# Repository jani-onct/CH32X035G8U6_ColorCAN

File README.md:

# ColorCAN

**ColorCANは，CH32X035G8U6内蔵のPIOCで1 MbpsのClassic CAN送信を実装したカラーセンサ基板です．** TCS34725FNで測定した赤・緑・青・Clearの値を送信します．基板シルクは **v1.0.0**，CANのハートビートで通知するプロトコル版は **1** です．

基板の配置図はKiCadの3D表示です．この表示ではカラーセンサとマイコンの実装位置がパッドで見えます．DIPスイッチの操作方向は，基板のシルクにある `ON=1` と `TERM ON` を参照してください．

## PIOCによるCAN送信

**PIOC（Programmable Protocol I/O Controller）** は，CH32X035に内蔵されたI/O制御用の8ビットコアです．メインCPUから独立して命令を実行し，ピンの出力と読み取りのタイミングをクロック単位で制御できます．[WCHのPIOC解説](https://www.cnblogs.com/wchmcu/p/17678765.html)

ColorCANのPIOC版FWでは，メインCPUがセンサを読み取り，CANフレームを組み立てます．PIOCはPC19（TX）からフレームを1ビットずつ出力し，PC18（RX）でバスの状態を読み返してACKを確認します．SN65HVD230がCAN_HとCAN_Lの差動信号を扱います．

## 動作の様子

<p><a href="https://github.com/jani-onct/CH32X035G8U6_ColorCAN/issues/1#issue-6348853291" target="_blank">動作の様子(動画)</a></p>

## 基板仕様

| 項目 | 仕様 |
|---|---|
| 外形・取付穴 | 30 × 28 mm，四隅に直径3.2 mmのM3用取付穴．穴の中心間隔は横24 mm × 縦22 mm |
| マイコン | WCH CH32X035G8U6，QFN-28 |
| カラーセンサ | ams OSRAM TCS34725FN．I²Cの7-bitアドレスは `0x29`．試験FWは積分時間50.4 ms，ゲイン1倍 |
| 照明・電源表示 | センサ両側の白色LED 2個，電源表示の赤色LED 1個 |
| 電源 | 5 V入力．XC6206P332MR-Gで基板内の3.3 Vを生成 |
| USB-C（J1） | 5 V給電，USB ISP書き込み，仮想COMでのデバッグ |
| CAN（J2） | JST XA 4極，2.5 mmピッチ，横型（S04B-XASK-1）．SN65HVD230使用，Rsは10 kΩでGNDへ接続 |
| DIP（SW1） | [OTAX KHS42E（秋月電子・108929）](https://akizukidenshi.com/catalog/g/g108929/)，4連．3連でノード番号，1連で120 ΩのCAN終端を設定 |

## 配線とDIP設定

**DIP面を手前にして，XAコネクタを下**に向けたとき，J2のピンは左から次の順です．

| ピン | シルク | 信号 |
|---:|---|---|
| 1 | `GND` | 電源・CAN共通GND |
| 2 | `+5V` | 5 V電源入力 |
| 3 | `L` | CAN_L |
| 4 | `H` | CAN_H |

**USB-CのVBUSとJ2の+5Vは基板上で同じネットです．給電元は片方にしてください．** USB給電でCANを試す場合は，J2のGND・CAN_L・CAN_Hを接続し，J2の+5Vを開放します．J2給電中にUSBデバッグする場合は，VBUSを切ったデータ用USBケーブルを使用します．

XAコネクタを下にした状態で，**左に倒すとON，右に倒すとOFF**です．上の3段で送信するCAN IDを選び，変更後に電源を入れ直します．

| 最上段（基板の `1`） | 2段目（`2`） | 3段目（`4`） | ノード番号 | RGBCのCAN ID | ハートビートのCAN ID |
|---|---|---|---:|---|---|
| OFF | OFF | OFF | 0 | `0x240` | `0x248` |
| ON | OFF | OFF | 1 | `0x241` | `0x249` |
| OFF | ON | OFF | 2 | `0x242` | `0x24A` |
| OFF | OFF | ON | 4 | `0x244` | `0x24C` |
| ON | OFF | ON | 5 | `0x245` | `0x24D` |
| OFF | ON | ON | 6 | `0x246` | `0x24E` |
| ON | ON | ON | 7 | `0x247` | `0x24F` |

一番下の `TERM` は120 Ω終端のスイッチです．CANバスの両端でONにします．

## CANを受信する

**1 Mbps，Classic CAN，標準11-bit ID，データ長8バイト．** 複数バイトの数値は下位バイトから並びます．

| フレーム | 送信タイミング |
|---|---|
| RGBC | 有効な測定値を取得できたとき，100 msごと |
| ハートビート | 約1秒ごと，またはセンサ状態が変化したとき |

1. ColorCAN 1台と，1 MbpsのCAN受信機1台を短い配線でつなぎます．CAN_H同士，CAN_L同士，GND同士を接続し，両端を120 Ωで終端します．
2. 受信機を通常モード（ACKあり）に設定します．まずID用DIPをすべてOFFにしてColorCANを起動すると，ノード番号は `0` です．
3. USB-CANアダプターなどの受信ツールで，`0x240` のRGBCと `0x248` のハートビートを確認します．

### CANメッセージの例

ID用DIPをすべてOFFにしたときの例です．

```text
CAN ID  DLC  データ（16進）
0x240     8  AB 00 B5 00 B8 00 14 02
0x248     8  01 01 0B 00 61 04 00 00
```

- **`0x240` RGBC** — 2バイトずつ読むと，R = 171，G = 181，B = 184，Clear = 532．
- **`0x248` ハートビート** — プロトコル版1，測定有効，測定成功11回，起動から1,121 ms．

各FWは**ColorCAN 1台が送信するベンチ試験用**です．複数の送信ノードが共存する運用バスに組み込むには，CANの調停，再送，エラー処理を備えた実装が必要です．ベンチ試験ではノード0の両フレームを受信確認済みです．

- [CAN仕様とデコード例](docs/CAN.md)
- [CANデータベース（DBC，ノード0〜7）](docs/ColorCAN.dbc)

### ch32fun版のTIM1＋DMAとPIOCのメモリ使用量

各FWのCAN ID，RGBCとハートビートのデータ形式，送信周期は共通です．

| ビルド時の使用量 | TIM1＋DMA版 | PIOC版 | 差（PIOC版 − TIM1＋DMA版） |
|---|---:|---:|---:|
| Flash | 7,112 B | 7,148 B | +36 B |
| メインCPUの静的RAM（`.data`＋`.bss`） | 1,564 B | 472 B | −1,092 B |
| メインCPUのRAM残り（スタック使用前） | 18,916 B | 15,912 B | −3,004 B |

PIOC版では，送受信に使っていたDMAバッファ計1,080 Bが不要になり，TIM1とDMAの2チャネルが空きます．PIOC命令は184 Bです．メインCPU用のRAMは16 KiBで，残りの4 KiBをPIOC用に予約しています．メインCPUは送信完了をポーリングします．CPU負荷とスタックのピーク使用量は未計測です．

ch32funのPIOC版を使った実機試験では，ノード0のRGBC（`0x240`）とハートビート（`0x248`）が1 Mbpsの受信機に届き，RGBCの受信カウンタが増えることを確認しました．

## ファームウェアの書き込み

ColorCAN v1.0.0（CH32X035G8U6）用です．ch32fun版は実機でCANを受信確認済みです．Arduino版はUSB ISPでの書き込みとベリファイを確認済みです．

| 実装 | 書き込み用HEX | SHA-256 |
|---|---|---|
| TIM1＋DMA版 | [colorcan_can_bench.hex](firmware/colorcan_can_bench.hex) | `e5137b95454fce0f72337260dc35df75672d55e5464d6f02d0543154b2a608ff` |
| PIOC版（ch32fun） | [colorcan_can_pioc.hex](firmware/colorcan_can_pioc.hex) | `1e422510251ff6a533be32441a781ffb076a6dc97d74cc8b8e29d4a9e3a904bd` |
| PIOC版（Arduino） | [colorcan_can_pioc_arduino.hex](firmware/colorcan_can_pioc_arduino.hex) | `d5f5aad851115a2fc54eebe81fec8b35ea951dc252fb6bb9a10da01881828f88` |

Arduino版のソースとビルド手順は[Arduino版FWの説明](firmware/arduino/README.md)を参照してください．

1. J2からの給電を外し，基板の `BOOT` を押しながらUSB-CをPCに接続します．
2. [wchisp](https://github.com/ch32-rs/wchisp) を使い，`wchisp --usb info` でチップが `CH32X035G8U6` と表示されることを確認します．
3. HEXをダウンロードしたフォルダで，選んだ版のコマンドを実行し，`Verify OK` を確認します．

**TIM1＋DMA版**

```sh
wchisp --usb flash colorcan_can_bench.hex
```

**PIOC版（ch32fun）**

```sh
wchisp --usb flash colorcan_can_pioc.hex
```

**PIOC版（Arduino）**

```sh
wchisp --usb flash colorcan_can_pioc_arduino.hex
```

書き込み後にUSBを挿し直す場合は，`BOOT` を押さずに接続すると通常起動します．

### ファームウェアに含まれる第三者コード

- ch32fun版には[ch32fun](https://github.com/cnlohr/ch32fun)が含まれます．[ch32funの著作権表示とMITライセンス全文](firmware/ch32fun-LICENSE.txt)
- Arduino版にはWCH Arduino Coreが含まれます．[ライセンスと対応ソース](firmware/arduino/README.md#ライセンスと対応ソース)

## デバッグ出力

Arduino版はPA2（TX）のUARTに115200 bpsで出力します．ch32fun版のログはUSB仮想COMで確認できます．

- 通常起動すると仮想COMポートにRGBCを約500 msごと，CAN送信の集計を約1秒ごとに出力します．COMポートの設定例は `115200` です．
- ログの `ACK` は送信中に確認したACKの件数，`NACK` はACKなし，`BUSY` は送信前にバスが空いていなかった回数，`ERR` は読み返し不一致やDMAエラーなどです．

## 基板内の信号

| 機能 | CH32X035側 | 接続先 |
|---|---|---|
| I²C | PA4（SCL），PA5（SDA） | TCS34725FN．各信号を4.7 kΩで3.3 Vへプルアップ |
| センサ割り込み | PA1 | TCS34725FNのINTに接続．試験FWはI²Cポーリングで測定 |
| CAN | PC19（TX），PC18（RX） | SN65HVD230のD，R |
| USB | PC16（D−），PC17（D+） | USB-C．BOOTボタンはPC17側に接続 |
| UARTテストパッド | PA2（TX），PA3（RX） | TP1，TP2 |

## 回路図・基板寸法図

編集用の[KiCad 9プロジェクト](kicad/)も公開しています．リポジトリをダウンロードし，`kicad/IRC27_ColorCAN_v1.0.0.kicad_pro` を開いてください．KiCadの標準ライブラリと，同梱のプロジェクト専用ライブラリを使います．

| ファイル | 内容 |
|---|---|
| [IRC27_ColorCAN_v1.0.0.kicad_pro](kicad/IRC27_ColorCAN_v1.0.0.kicad_pro) | プロジェクトと設計ルール |
| [IRC27_ColorCAN_v1.0.0.kicad_sch](kicad/IRC27_ColorCAN_v1.0.0.kicad_sch) | 回路図 |
| [IRC27_ColorCAN_v1.0.0.kicad_pcb](kicad/IRC27_ColorCAN_v1.0.0.kicad_pcb) | 基板レイアウト |

KiCadの3D表示はインストール済みのモデルを使います．USB-CとXAコネクタの個別モデルは手元のKiCadで追加できます．外観の確認にはREADME冒頭の3D画像も使えます．

[回路図・基板図ビューワ](https://kicanvas.org/?github=https://github.com/jani-onct/CH32X035G8U6_ColorCAN/tree/main/kicad)  
※外部サイトが開きます

### 回路図

### 基板寸法図

寸法の単位はmmです．基板外形は横30 × 縦28，取付穴の中心間隔は横24 × 縦22です．

## 部品資料

- [WCH CH32X035](https://github.com/openwch/ch32x035)
- [ams OSRAM TCS3472データシート](https://look.ams-osram.com/m/7ec5bcc3e40679be/original/TCS3472-DS000390.pdf)
- [TI SN65HVD230データシート](https://www.ti.com/lit/ds/symlink/sn65hvd230.pdf)
- [OTAX KHSシリーズ](https://www.otax.co.jp/service/khs/)

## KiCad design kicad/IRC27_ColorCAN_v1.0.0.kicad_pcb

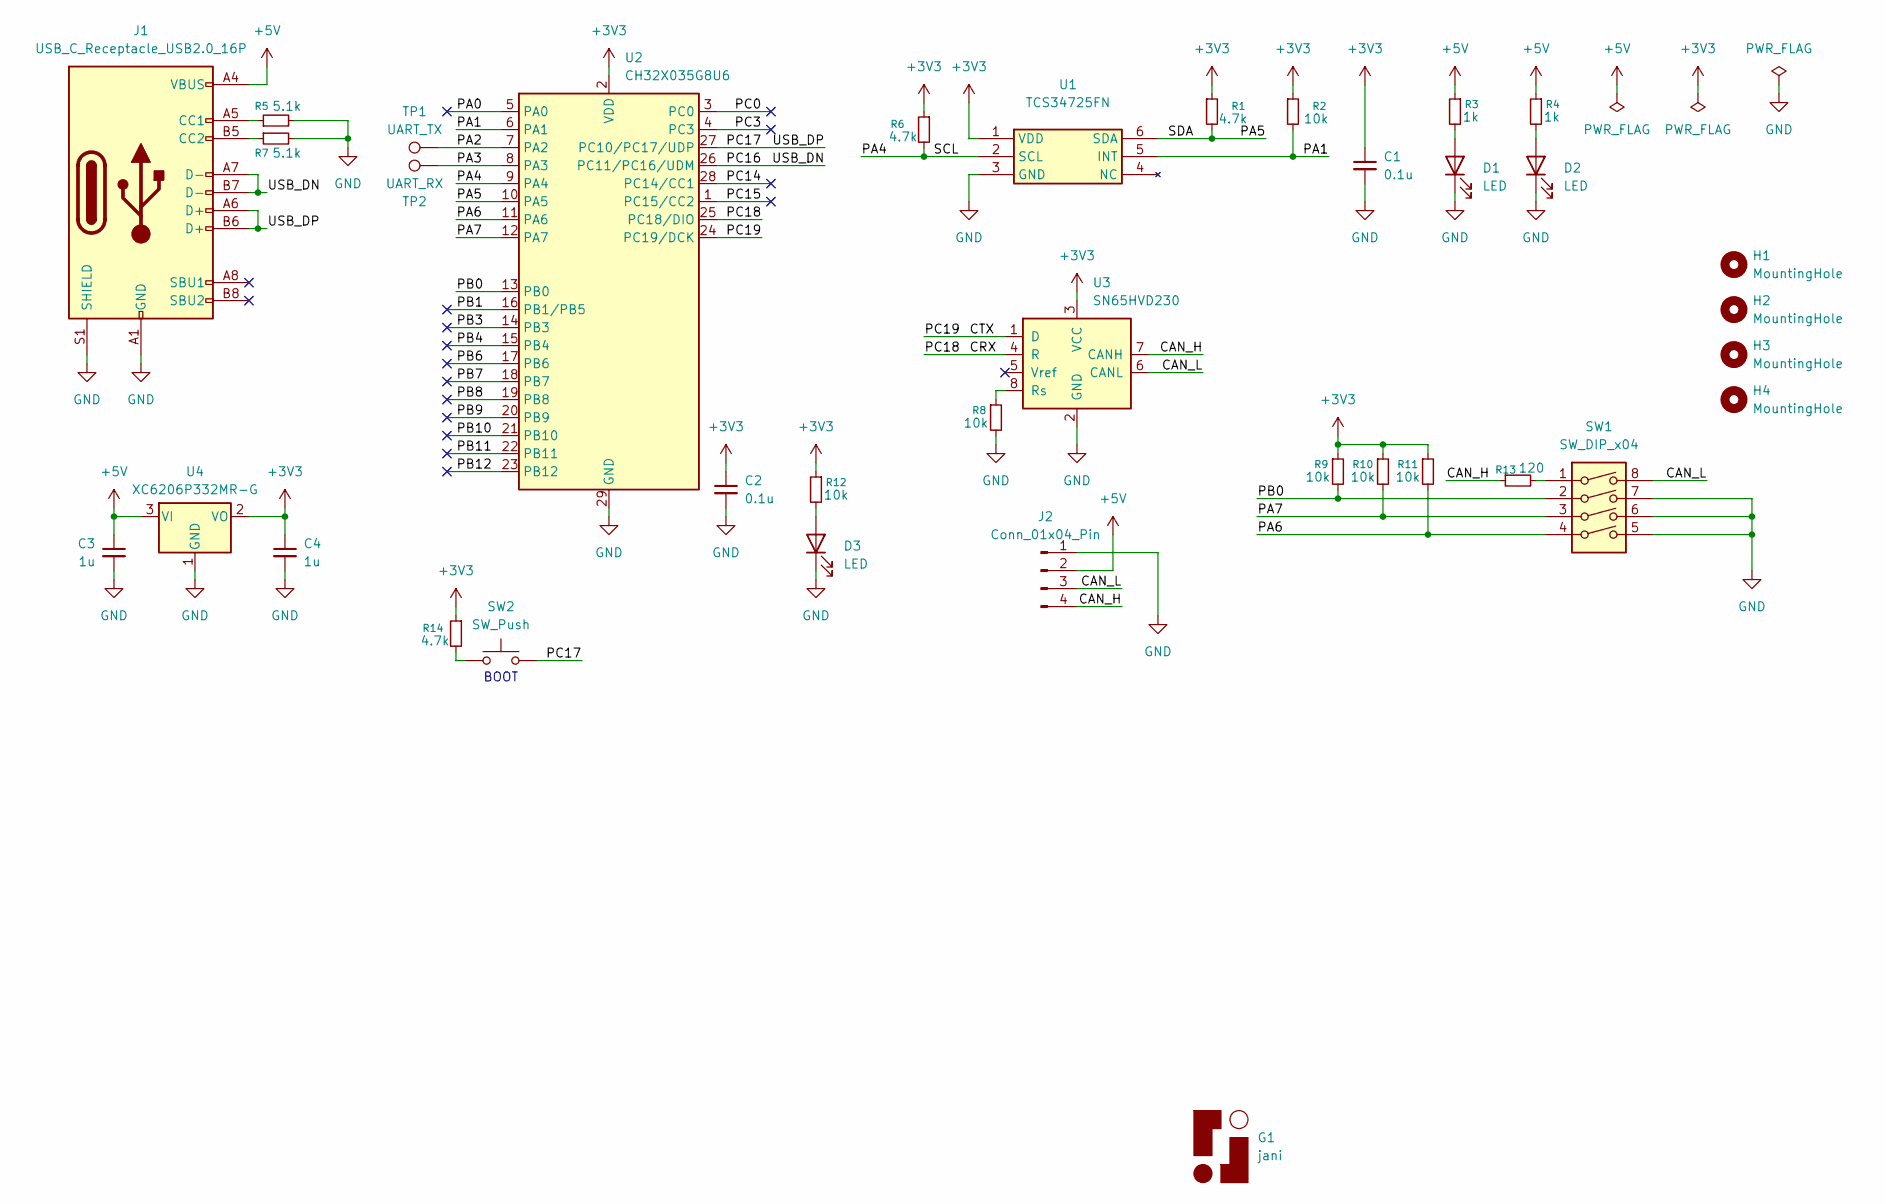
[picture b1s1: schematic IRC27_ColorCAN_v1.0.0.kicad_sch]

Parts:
C1, C2: 0.1u; C_0603_1608Metric
C3, C4: 1u; C_0603_1608Metric
D1, D2, D3: LED; LED_0603_1608Metric
G1: jani; jani_rogo_mini
H1, H2, H3, H4: MountingHole; MountingHole_3.2mm_M3
J1: USB_C_Receptacle_USB2.0_16P; USB_C_Receptacle_HRO_TYPE-C-31-M-12
J2: Conn_01x04_Pin; JST_XA_S04B-XASK-1_1x04_P2.50mm_Horizontal
R1, R6, R14: 4.7k; R_0402_1005Metric
R2, R8, R9, R10, R11, R12: 10k; R_0402_1005Metric
R3, R4: 1k; R_0402_1005Metric
R5, R7: 5.1k; R_0402_1005Metric
R13: 120; R_0603_1608Metric
SW1: SW_DIP_x04; SW_DIP_SPSTx04_Slide_KingTek_DSHP04TS_W7.62mm_P1.27mm
SW2: SW_Push; SW_Push_SPST_NO_Alps_SKRK
TP1: UART_TX; TestPoint_Pad_D1.0mm
TP2: UART_RX; TestPoint_Pad_D1.0mm
U1: TCS34725FN; Manufacturer_Part_Number TCS34725FN; Mouser Part Number 985-TCS34725FN
U2: CH32X035G8U6; WQFN-28-1EP_4x4mm_P0.4mm_EP2.7x2.7mm
U3: SN65HVD230; SOIC-8_3.9x4.9mm_P1.27mm
U4: XC6206P332MR-G; SOT-23-3

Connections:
+3V3: C1.1, C2.1, C4.1, R1.1, R2.1, R6.1, R9.1, R10.1, R11.1, R12.1, R14.1, U1.1 (VDD), U2.2 (VDD), U3.3 (VCC), U4.2 (VO)
+5V: C3.1, J1.A4 (VBUS), J1.A9 (VBUS), J1.B4 (VBUS), J1.B9 (VBUS), J2.2, R3.1, R4.1, U4.3 (VI)
/CAN_H: J2.4, R13.1, U3.7 (CANH)
/CAN_L: J2.3, SW1.8, U3.6 (CANL)
/CRX: U2.25 (PC18/DIO), U3.4 (R)
/CTX: U2.24 (PC19/DCK), U3.1 (D)
/PA0: U2.5 (PA0)
/PA1: R2.2, U1.5 (INT), U2.6 (PA1)
/PA2: TP1.1, U2.7 (PA2)
/PA3: TP2.1, U2.8 (PA3)
/PA4: R6.2, U1.2 (SCL), U2.9 (PA4)
/PA5: R1.2, U1.6 (SDA), U2.10 (PA5)
/PA6: R11.2, SW1.4, U2.11 (PA6)
/PA7: R10.2, SW1.3, U2.12 (PA7)
/PB0: R9.2, SW1.2, U2.13 (PB0)
/PB1: U2.16 (PB1/PB5)
/PB3: U2.14 (PB3)
/PB4: U2.15 (PB4)
/PB6: U2.17 (PB6)
/PB7: U2.18 (PB7)
/PB8: U2.19 (PB8)
/PB9: U2.20 (PB9)
/PB10: U2.21 (PB10)
/PB11: U2.22 (PB11)
/PB12: U2.23 (PB12)
/PC0: U2.3 (PC0)
/PC3: U2.4 (PC3)
/PC14: U2.28 (PC14/CC1)
/PC15: U2.1 (PC15/CC2)
/PC16: J1.A7 (D-), J1.B7 (D-), U2.26 (PC11/PC16/UDM)
/PC17: J1.A6 (D+), J1.B6 (D+), SW2.2, U2.27 (PC10/PC17/UDP)
GND: C1.2, C2.2, C3.2, C4.2, D1.1 (K), D2.1 (K), D3.1 (K), J1.A1 (GND), J1.A12 (GND), J1.B1 (GND), J1.B12 (GND), J1.S1 (SHIELD), J2.1, R5.2, R7.2, R8.2, SW1.5, SW1.6, SW1.7, U1.3 (GND), U2.29 (GND), U3.2 (GND), U4.1 (GND)
unnamed: D1.2 (A), R3.2
unnamed: D2.2 (A), R4.2
unnamed: D3.2 (A), R12.2
unnamed: J1.A5 (CC1), R5.1
unnamed: J1.B5 (CC2), R7.1
unnamed: R13.2, SW1.1
unnamed: R14.2, SW2.1
unnamed: R8.1, U3.8 (Rs)

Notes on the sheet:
BOOT

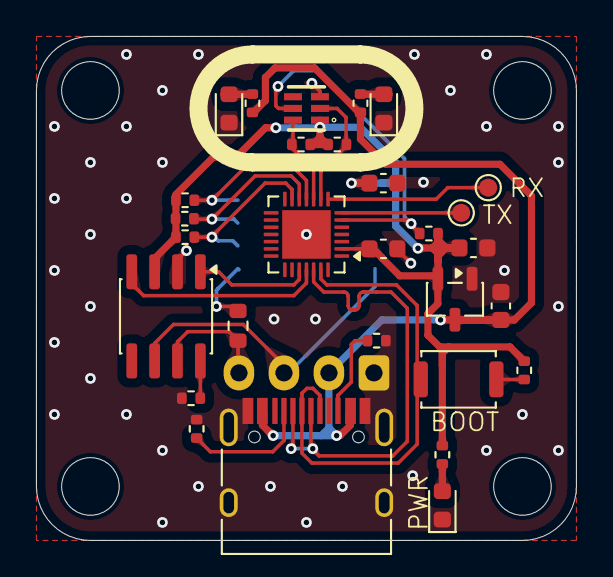
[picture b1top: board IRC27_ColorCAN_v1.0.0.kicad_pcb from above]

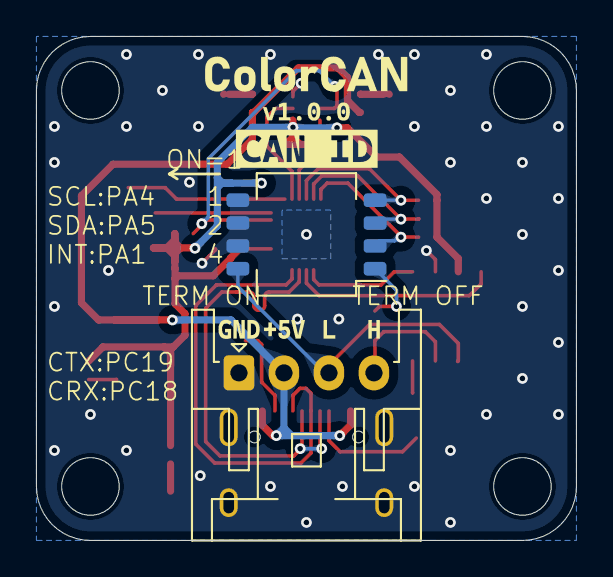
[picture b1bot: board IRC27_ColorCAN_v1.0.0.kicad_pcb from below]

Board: 2 copper layers, 30.0 x 28.0 mm, 36 parts (2 on the bottom side), 25 nets.

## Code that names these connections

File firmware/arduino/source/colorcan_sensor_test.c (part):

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#include <string.h>
#endif

// ColorCAN v1.0.0: U2 PA4=SCL, PA5=SDA. External pull-ups are fitted.
#define TCS_ADDR 0x29u
#define TCS_ID 0x44u
#define CMD 0x80u
#define AUTO_INCREMENT 0x20u

static uint8_t scl = PA4;
static uint8_t sda = PA5;

// Keep the output latch low. A released line is an input and rises through
// the board's 4.7 kOhm resistor. The MCU never actively drives a high level.
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
static void diagnose_bus(void)
{
    bool pa4 = check_line(PA4, PA5);
    bool pa5 = check_line(PA5, PA4);
    printf("DIAG GPIO PA4=%s PA5=%s\r\n", pa4 ? "OK" : "FAIL", pa5 ? "OK" : "FAIL");
    if (!pa4 || !pa5) return;

    scl = PA5;
    sda = PA4;
    uint8_t id;
    if (sensor_read(0x12, &id, 1) && id == TCS_ID) {
        printf("DIAG sensor detected with SCL=PA5 SDA=PA4\r\n");
        return;
    }
    scl = PA4;
    sda = PA5;

    unsigned count = 0;
    for (uint8_t address = 0x08; address <= 0x77; ++address) {
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
static uint8_t read_node(void)
{
    funPinMode(PA6, GPIO_CFGLR_IN_FLOAT);
    funPinMode(PA7, GPIO_CFGLR_IN_FLOAT);
    funPinMode(PB0, GPIO_CFGLR_IN_FLOAT);
    Delay_Ms(20);
    return (uint8_t)((!funDigitalRead(PA6)) | ((!funDigitalRead(PA7)) << 1)
                   | ((!funDigitalRead(PB0)) << 2));
}

static uint32_t uptime_ms(void)
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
